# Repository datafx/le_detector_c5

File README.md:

# LE Gear Detector — XIAO ESP32-C5 Fork

Passive 5GHz/2.4GHz WiFi + BLE scanner for law-enforcement equipment,
rebuilt for the Seeed XIAO ESP32-C5 to add 5GHz detection. The original
project ([`datafx/le_detector`](https://github.com/datafx/le_detector),
ESP32-WROOM-32U) is 2.4GHz only and can't see the highest-value target
found in the field: Axon Fleet Hub units broadcasting their own hidden APs
on 5GHz. A match signals with a flashing red screen border + buzzer,
faster as the signal strengthens.

## Hardware

| Part | Notes | Link |
|---|---|---|
| Seeed Studio XIAO ESP32-C5 | RISC-V, dual-band WiFi 6 (2.4+5GHz), BLE 5, USB-C | [Seeed Studio](https://www.seeedstudio.com/Seeed-Studio-XIAO-ESP32C5-p-6609.html) |
| 2.8" ILI9341 TFT, SPI, 240×320, with XPT2046 touch + microSD slot | Standard combo board sold under many names; touch and SD are present on the board but not yet used by this firmware | search "2.8 inch ILI9341 SPI touch SD" |
| Active buzzer module, 3-pin (VCC/GND/signal) | Must have its own driver transistor onboard. Confirmed **active-low** on this build — check `BUZZER_ACTIVE_LOW` in `config.h` against yours | search "active buzzer module 3 pin" |
| Alfa APA-M25 dual-band antenna | 8 dBi @2.4GHz / 10 dBi @5GHz, RP-SMA | [Alfa Network](https://alfa-network.eu/apa-m25) |
| U.FL → RP-SMA pigtail | Connects the XIAO's onboard U.FL to the external antenna | search "U.FL RP-SMA pigtail" |
| Breadboard + jumper wires | | |
| USB-C cable | Power + programming | |

The display, buzzer, and pigtail are generic commodity parts sold by many
sellers under many names — there's no single canonical listing worth
linking (and one that works today can vanish tomorrow), so a search term
is given instead of a storefront link.

## Wiring

Pin assignments confirmed against the physical board — see `CLAUDE.md`
decision #6 for the full reasoning, including which pins were deliberately
avoided and why (boot-strap pins, reserved for a future GPS UART, etc.).

| Signal | XIAO pin | GPIO | Notes |
|---|---|---|---|
| Display `VCC` | `5V` | — | needs the 5V/VBUS pin specifically, not `3V3` |
| Display `GND` | `GND` | — | |
| Display `LED` (backlight) | `5V` | — | tied permanently on |
| Display `CS` | `D2` | 25 | |
| Display `DC` | `D3` | 7 | |
| Display `RESET` | `D4` | 23 | |
| Display `SDI`/MOSI | `D10` | 10 | shared SPI bus |
| Display `SCK` | `D8` | 8 | shared SPI bus |
| Display `SDO`/MISO | `D9` | 9 | shared SPI bus |
| `SD_CS` | `D5` | 24 | wired and reserved — SD support isn't built yet |
| `SD_MOSI`/`SD_MISO`/`SD_SCK` | `D10`/`D9`/`D8` | 10/9/8 | shared with the display |
| Buzzer `VCC` | `3V3` | — | |
| Buzzer `GND` | `GND` | — | |
| Buzzer signal | `D0` | 1 | |

Touch (`T_CLK`/`T_CS`/`T_DIN`/`T_DO`/`T_IRQ`) is present on the display
board but intentionally unwired — planned for future bench-configuration
tooling, not for driving controls.

## Build & flash

PlatformIO has no ESP32-C5 support as of this writing — this project
builds via the Arduino IDE / `arduino-cli` instead.

### Arduino IDE

1. **Install the ESP32 board package.** File → Preferences → Additional
   Boards Manager URLs, add:

       https://raw.githubusercontent.com/espressif/arduino-esp32/gh-pages/package_esp32_index.json

   Then Tools → Board → Boards Manager, search "esp32", install **esp32 by
   Espressif Systems**, version **3.3.5 or higher** (built and tested
   against 3.3.11).

2. **Select the board:** Tools → Board → esp32 → **XIAO_ESP32C5**.

3. **Install libraries** via Library Manager: `Adafruit GFX Library`,
   `Adafruit BusIO`, `Adafruit ILI9341`. BLE support is bundled with the
   esp32 core itself — no separate BLE library install needed.

4. **Open the sketch:** `firmware/le_detector_c5/le_detector_c5.ino`.
   Every `.cpp`/`.h` file in that same folder is compiled and linked
   automatically — Arduino sketches don't use PlatformIO's `src`/`include`
   split, so everything lives flat in one folder.

5. **Plug in the board** via USB-C, select its port, and upload.

### arduino-cli

    arduino-cli core update-index
    arduino-cli config set board_manager.additional_urls https://raw.githubusercontent.com/espressif/arduino-esp32/gh-pages/package_esp32_index.json
    arduino-cli core install esp32:esp32@3.3.11
    arduino-cli lib install "Adafruit GFX Library" "Adafruit ILI9341"
    arduino-cli compile --fqbn esp32:esp32:XIAO_ESP32C5 firmware/le_detector_c5
    arduino-cli upload -p /dev/ttyACM0 --fqbn esp32:esp32:XIAO_ESP32C5 firmware/le_detector_c5

### If upload fails, or the board doesn't show up as a serial port

The C5 uses its SoC's own native USB-Serial/JTAG peripheral, not a separate
USB-serial chip — no CH340/CP210x driver needed — but that comes with its
own gotchas, all hit and resolved during this project's own bring-up:

- **Linux: the `cdc_acm` kernel module.** If `/dev/ttyACM0` never appears,
  check `lsmod | grep cdc_acm`; if missing, `sudo modprobe cdc_acm` (if
  *that* fails with "module not found," your running kernel doesn't match
  what's installed on disk — reboot). Your user also needs permission on
  the port: group `dialout` on Debian/Ubuntu, `uucp` on Arch-based distros.
- **Upload fails with "Invalid head of packet" or "Serial data stream
  stopped: possible serial noise or corruption."** Looks like a code or
  board problem, usually isn't — a USB hub between the board and the
  computer was the actual cause here. Plug directly into a root/motherboard
  port before suspecting anything else.
- **No serial monitor output.** `arduino-cli monitor` produced nothing in
  testing even with the board clearly running. On Linux, plain
  `cat /dev/ttyACM0` worked reliably instead, and conveniently triggers a
  fresh reset on open. This firmware doesn't print anything during normal
  operation anyway (the display is the real status output), so this mostly
  matters if you're debugging.

## Watchlist

**62 OUI entries** across law-enforcement radio, body/dash cam, vehicle
router/MDT, radar/lidar, ALPR, and lightbar equipment, plus **6 SSID
patterns** (5 real + one test/demo row). The full list, provenance, and
vendor-collision reasoning live as comments in the source files themselves
— those are what actually runs, so they're the version that can't drift out
of sync with reality:

- [`oui_table.cpp`](firmware/le_detector_c5/oui_table.cpp) — MAC OUI
  watchlist
- [`ssid_table.cpp`](firmware/le_detector_c5/ssid_table.cpp) — SSID
  watchlist (beacons, probe requests, probe responses)

A few vendors are **disabled by default** after field testing showed they
false-positive more than they help — commented out, not deleted, so each
is one edit away from re-enabling if that read ever turns out wrong:
**CradlePoint**, **Peplink**, **Pepwave**, **Vantiva**, **PRO-VISION**.
Comment a row back in (or out) to change what's active for most entries;
CradlePoint specifically is gated by an `EXCLUDE_VENDOR_CRADLEPOINT` toggle
at the top of `oui_table.cpp`. Run `test/test_oui.cpp` after any edit.

Want to test a local addition before submitting it upstream? Drop it in
`user_oui_table.cpp` instead — unsorted, just appended to.

### SSID watchlist

| Pattern | Label | Category |
|---|---|---|
| `PSP-MVR`    | PSP in-car video          | Body/car cam |
| `SP-MVR`     | PSP paired virtual AP     | Other |
| `PSP-TEST`   | PSP facility              | Other |
| `PSPWLAN`    | PSP facility              | Other |
| `PSP_UC`     | PSP facility voice        | Other |
| `LEDET-TEST` | TEST/DEMO — not real gear | Other |

All PSP rows are prefix matches, deliberately — a substring `CONTAINS
"PSP"` rule tested against real survey data matched several unrelated
civilian networks near the same facilities (a pet store, a retailer, a
private residence). The full prefix string, not the shared `PSP` fragment,
is what makes these safe to alert on. Same logic for `SP-MVR` vs.
`PSP-MVR`: kept as two explicit rows rather than one `CONTAINS "SP-MVR"`
rule, which would also match `PSP-MVR` (it contains "SP-MVR" as a
substring).

**Provenance:** confirmed via WiGLE survey data cross-checked against
three independent Pennsylvania State Police barracks in three different
troops, roughly 280km apart, all on matching Cisco hardware.
`PSP-MVR`/`SP-MVR` (Mobile Video Recorder, PSP's in-car video system) and
`PSP-TEST` were confirmed at all three sites; cross-site BSSID correlation
— matching Cisco OUI sub-ranges across independently surveyed locations,
not just a shared naming convention — confirms a single statewide
deployment, not coincidence. `PSPWLAN`/`PSP_UC` were observed at one site
only, so carry lower confidence until cross-checked elsewhere. Exact survey
locations and dates are kept in local, non-public notes rather than this
file.

**Known limitation:** these are fixed APs at barracks buildings, not
vehicle-mounted equipment. A hit on the road means a cruiser's in-car
client is directedly probing for one of these SSIDs while out of range of
the real AP — whether PSP in-car systems actually do that is untested in
the field. Treat a hit here as barracks-proximity, not confirmed mobile
detection, until that's verified.

## Confirmed agencies

| Agency | Status |
|---|---|
| Pennsylvania State Police (PSP) | Confirmed in the field by the project author |

That's the only agency confirmed so far, but detection isn't tied to PSP.
The strongest target, Axon Fleet in-car hubs, broadcast their own WiFi
access point on 5GHz from Axon's registered MAC prefix (`00:25:DF`), and the
detector matches that prefix rather than anything agency-specific. **Any
agency running in-car Axon WiFi APs should be picked up the same way.** The
same goes for the other OUI entries: they match the equipment maker, not
the department. The PSP SSID rows are the exception, since those names are
specific to PSP.

If you've confirmed a hit on another agency, see
[Contributing](#contributing) so it can be added here.

## How detection works

A three-band phase machine — only one of WiFi-5GHz / WiFi-2.4GHz / BLE can
be up at a time (one radio behind a dual-band diplexer, and it can't do
WiFi and BLE simultaneously either). Scheduling is 5GHz-dominant, based on
real drive data and a measured radio-switch cost on this specific board:

- **5GHz** sweeps continuously (9 non-DFS channels, ~2.7s/sweep) — the
  only long-range, continuous signal (beacons every ~100ms), and the
  primary detection path.
- **BLE** gets a short 400ms dip every 3rd 5GHz sweep, not every cycle —
  its realistic job is a close/stopped encounter lasting several seconds,
  not a sub-second highway pass, so it doesn't need constant attention.
- **2.4GHz** gets a brief 3-channel token check (1/6/11 only) every 8th
  sweep — contributes almost nothing on the road per the drive data (a
  barracks-proximity signal, not a mobile one), kept only as an occasional
  check.

Measured WiFi↔BLE switch cost on this board: **103ms** to switch into BLE,
**9ms** back out, with zero measured variance across repeated runs. See
[`firmware/05_radio_switch_timing/`](firmware/05_radio_switch_timing/) to
re-measure on different hardware. The "every N sweeps" cadence constants
(`BLE_EVERY_N_SWEEPS`, `WIFI_2G_EVERY_N_SWEEPS` in `config.h`) are starting
points to tune empirically, not a measured optimum.

A match's alert shows which band/radio caught it — e.g. "via 5GHz WiFi
OUI" or "SSID beacon (2.4GHz): PSP-MVR" — useful for telling a long-range
hit apart from a close BLE encounter at a glance.

## Known limits

- **One radio, three bands, time-sliced.** Only one of 5GHz WiFi / 2.4GHz
  WiFi / BLE is ever listening — during any other phase, that band is
  invisible. See "How detection works" above for the current schedule.
- **MAC randomisation.** Only public BLE addresses and non-randomised WiFi
  MACs carry a real OUI — randomised addresses are skipped, since their
  vendor bits are meaningless. SSID matching runs independently of this
  and is unaffected.
- **PSP SSID rows are barracks-proximity, not confirmed mobile detection.**
  See SSID watchlist provenance above.
- **SSID matching depends on what's actually broadcast.** A wildcard probe
  or hidden-SSID beacon carries no SSID bytes at all — nothing to match
  either way. Directed probe requests are a declining signal on modern
  phones (randomised MAC + wildcard probes only, roughly iOS/Android 2014-
  2017 onward), so this increasingly only catches older/embedded clients.
  Beacon/probe-response matching is unaffected by that trend.
- **No SD card support yet.** The display board has a microSD slot and the
  select pin (`SD_CS`) is wired, but CSV-based config/logging isn't built —
  the firmware runs entirely on its compiled-in tables for now.

## Tuning

Everything lives in `firmware/le_detector_c5/config.h`: band/channel
lists, sweep cadence, flash-rate endpoints (`RSSI_WEAK`/`RSSI_STRONG`,
`FLASH_PERIOD_SLOW`/`FAST`), alert hold time, and `BUZZER_ENABLED` for
silent bench testing.

## Contributing

The watchlist is only as good as the field data behind it, and the most
useful thing you can contribute is **[Kismet](https://www.kismetwireless.net/)
captures recorded near police vehicles**. If you can make some, get in
touch and I'll analyze them for OUIs and SSIDs worth adding.

- **More than one sample, from different areas, is much more useful than
  one.** A single capture can't separate a department's gear from whatever
  else happened to be nearby. Several captures from different places,
  vehicles or agencies show what they have in common, which is what makes
  a reliable watchlist entry.
- **Capture both bands.** Use an adapter that covers 5GHz as well as
  2.4GHz; the in-car gear that matters most is on 5GHz. Bluetooth is a
  bonus if your setup supports it.
- **Note the context** for each capture: date and time, rough location,
  the agency, and what was nearby (parked cruiser, passing traffic,
  barracks lot).
- **Don't post captures publicly.** They contain the MAC addresses and
  network names of everyone nearby, not just the police gear. Open a
  [GitHub issue](https://github.com/datafx/le_detector_c5/issues)
  to make contact, and we'll arrange a private way to send the files.
- **Listen only, from where you're allowed to be.** Kismet's default
  passive capture is all that's needed. Don't follow vehicles or get in
  the way of anyone working.

Watchlist changes land here first, with the unit test in
`test/test_oui.cpp`, and are then copied to the
[Waveshare port](https://github.com/datafx/le_detector_waveshare_c5). Bug
reports and fixes are welcome as issues or pull requests.

## License

GPLv3 (see `LICENSE`), matching the companion `rf_stalker` and
`police_oui_watchlist` projects, and the upstream `le_detector` project
this is forked from.

[`firmware/le_detector_c5/detector.cpp`](firmware/le_detector_c5/detector.cpp)
carries its own `SPDX-License-Identifier: MIT` line for the portions
adapted from nyanBOX — see the header comment in that file for exactly
what was adapted and what changed. Everything else in this repo is GPLv3.

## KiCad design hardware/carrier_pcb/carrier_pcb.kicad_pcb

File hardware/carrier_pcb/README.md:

# Carrier PCB — WORK IN PROGRESS, NOT FINISHED

Do not fabricate this board as-is. A physical prototype of the previous
revision was built and bench-tested - display, buzzer, and routing all
confirmed working - but that hands-on assembly surfaced real mechanical
issues (board length *and* J2 spacing, J3 position; see below), now
fixed and fully re-routed (0 unconnected items). This corrected revision
hasn't been physically built yet - see "What's NOT done."

## Mounting: held by the header, not screwed to the case

This board has **no mounting holes**. Earlier drafts gave it the same 4
holes as the display module, so it could bolt to the case's existing
corner bosses — but that only works by stacking both boards on the same
4 screws, which needs standoffs/spacers between them and a case
modification to deepen the bosses. Given how light this assembly is
(PCB + XIAO + buzzer), that's not worth it: the board is instead held
purely by its header engagement with the display board above it (which
keeps screwing to the case exactly as it did before this board existed).
If real-world vibration ever proves that insufficient, a dab of hot glue
between the two boards is the cheap fix — not designed in up front.

**History: chamfer → notch → narrowed board, each one fitting the real
case better than the last.** The first version used a 6mm diagonal
chamfer at each corner, sized off the display's datasheet hole margins
with no real measurement of the boss itself. A 1:1 scale printout
test-fit against the real case showed it wasn't close - the boss is a
rounded square, not the slim post the chamfer assumed. Measured it
properly off the case STL (top-down render, self-calibrated against the
model's own exact bounding box, not an assumed scale): roughly **7-8mm
across**. Switched to a square notch sized as large as the layout
allowed (7.3mm, capped by J1's own pad clearance) - still about 1mm
short of what the boss needed, an acknowledged unresolved gap at the
time.

**Resolved differently: don't dodge the bosses, don't reach them at
all.** User measured the case's actual clear channel between the two
bosses directly: **36.3mm wide** (the board's full 86mm length is fine,
the case was never tight there). The board became a **plain rectangle,
36.3mm × 86mm**, centered on J1 (which is the single widest feature at
33.02mm) rather than matching the display's full 50mm width. This
sidesteps the boss problem entirely instead of cutting around it - no
corner notches needed, and it also incidentally resolved a DRC
clearance warning on a user-routed TFT_SCK trace that had been sitting
close to the old, bigger notch. J1 keeps 1.04mm of copper-to-edge
clearance on each side (comfortably above the 0.5mm minimum), and J2/U1/
J3 were already well inside this narrower footprint with no changes
needed.

**Trimmed again: top edge pulled in to put J2 right on the edge too,
mirroring J1.** J1 sits 2.0mm (pin-center-to-edge) from the bottom edge.
J2 was still 4.96mm from the top edge, leaving unused board above it.
Pulled the top edge in to the same 2.0mm margin: new top edge at
**y=2.96** (was y=0), so the board is now **36.3mm × 83.04mm**. J2 gets
the same 1.40mm copper-to-edge clearance J1 already had. Both edits
(width and this height trim) were applied by editing the outline
directly in the routed file rather than regenerating from the script,
each time confirming no existing trace/via fell outside the new
boundary before committing to it - preserved all 64 of the user's
hand-routed segments through both changes, verified via DRC (0 errors)
each time.

**Now physically confirmed - and that confirmation found two more real
issues.** A physical prototype of the board (narrowed width, trimmed
top edge) was built and bench-tested: display, buzzer, and routing all
worked. But mounting the real display on the real board surfaced a
mechanical problem the digital fit couldn't catch: **the board was too
short, and the display sat tilted rather than straight.**

**First attempt at the fix was wrong - extending the board outline
alone doesn't change anything mechanically.** Initial diagnosis:
insufficient board material above J2 to physically back/support the
display once both headers were engaged. Extended the top edge back out
by 2mm (y=2.96 -> y=0.96) without moving J2 itself. User caught this
immediately: J2's position relative to J1 - the actual thing that
determines whether two header rows line up with the real display's true
spacing - never changed, so nothing about the mechanical fit could have
changed either; the board was just bigger, the tilt was still there.
**Real fix: move J2 the same 2mm, same direction, right along with the
edge** (y=4.96 -> 2.96) - not just extend the board around it. This
restores J2's margin-from-edge to exactly 2.0mm (matching J1's margin
again, same relationship as the original "J2 sits on the edge like J1"
decision) and - the part that actually matters mechanically -
**increases the J1-to-J2 spacing by 2mm** (79.04mm -> 81.04mm), which is
what a header-spacing mismatch against the real display would need.
Board is now **36.3 x 85.04mm**. J2 carries no electrical connections
(see below), so this move touched zero routing - verified via DRC (0
errors, segment/via count unchanged before and after).

**Also moved J3 (buzzer) closer to J1** (y=68 -> y=78, x unchanged) -
the real XIAO's USB-C connector was crowding the buzzer's right-angle
header in practice, something the digital layout didn't surface either
since courtyard-only clearance checks don't capture a mated cable's
real footprint. Moving J3 toward J1 trades its distance from U1's USB-C
area for more working room. Verified clear of J1's own pads (4.8mm
copper clearance) via DRC.

**Routing cost of this move: not trivial.** GND, BUZZER_SIG, and 3V3
are the only nets that touch J3, so only those needed clearing (12
segments + 2 vias, out of 41 total) - the other 26 segments (all the
TFT_* signal routing, untouched) survived intact. But GND turned out to
use J3's own pad as the junction point connecting J1 and U1's GND
together, not just a branch to J3 - so re-routing GND means redoing the
full 3-way connection, not just adding one short new segment. Checked
for other-net collisions at J3's new position before moving it (a TFT_CS
trace runs close by at x=15.71, confirmed 0.93mm clear) - also caught
and fixed a new silkscreen-over-copper warning from J3's own label
landing too close to J1's row in the tighter gap; moved the label to
the now much-larger open space on J3's other side instead.

**Still needs**: re-routing GND/BUZZER_SIG/3V3 (flagged above), and a
fresh physical test-fit of this corrected board - the tilt and USB-C
crowding were real-hardware findings, but this specific fix hasn't been
built yet.

## U1 (XIAO socket): footprint was wrong, now matches the real device

The original U1 footprint was a generic guess — two rows of 7 pins,
7.62mm apart, pins at `i*2.54mm` within each row — never checked against
the real XIAO ESP32-C5's actual pinout, and not mirrored for back-side
mounting. User caught both problems: wrong footprint, and backwards for
how the device actually gets plugged in (XIAO mounts on the board's
back, opposite the display).

**Fixed using Seeed's own official files**, not another guess:
downloaded their published KiCad footprint
(`XIAO-ESP32-C5-DIP.kicad_mod`) and schematic symbol from the
[XIAO KiCad library](https://wiki.seeedstudio.com/XIAO_BLE/) (same
family covers every XIAO board). The real footprint has **15.24mm**
between the two pin rows, not 7.62mm — a completely different part of
the board was being used. Cross-referenced the symbol to get the
real pin-number-to-signal mapping (D0–D6 on one row, D7–D10 + 3V3_OUT/
GND/VBUS on the other, in that specific order — not a clean split).

**Mirroring**: a part mounted on the back layer needs its footprint
mirrored left-right relative to how it would sit on the front — this is
what KiCad does automatically when you flip a footprint in the GUI, but
since this one was hand-authored as raw coordinates, that mirroring had
to be applied by hand too, and wasn't. Verified the mirror direction
using Seeed's own front and back pinout diagrams for the XIAO (they
publish both specifically because this flip is easy to get backwards) -
confirmed the two diagrams are exact left-right mirrors of each other
before trusting the derivation.

**Routing cleared, not preserved, for this one.** Unlike the earlier
outline-only changes (width, height trims), this moves the pads
themselves, and nearly every net touches U1 directly or routes through
it - preserving any of the old routing wasn't realistic. Pulled all 64
track/via segments rather than leave something uncertain in place.
Board is back to a clean, DRC-verified ratsnest (0 errors, 12
unconnected items, matching the exact pre-routing baseline) - **needs a
full re-route**.

**Slid toward the board's right edge** for USB-C cable clearance, as
far as the *real device's physical body* allows - not just its pads.
The pads alone would have permitted sliding further right, but the
actual XIAO module extends ~2.8mm beyond its own pin span on each side;
checking pads only would have let the real part hang ~1.3mm off the
board edge. Capped at **x=32** (board right edge minus the real
courtyard extent minus a 0.5mm margin), not x=34.

**Flagging, not deciding, one open question**: with this as a straight
slide (no rotation), the XIAO's USB-C port faces *inward* (toward
x≈21-23, the board's open left-center area), not toward the right edge
itself - it's the *blank far end* of the device that now sits near the
right edge. This still frees up real approach space for a cable (the
whole left side of U1's row is now open board), but if the port itself
needs to be at/past the edge, that needs a 180° rotation on top of the
slide, which hasn't been done - flagging it rather than guessing, since
it changes which end of the board needs clearance.

## J3 (buzzer socket): pin order changed, moved left, now a right-angle header

**Pin order**: was VCC/GND/SIG (pins 1/2/3). Changed to **GND/SIG/VCC**
(pins 1/2/3) to match the physical pinout of the actual buzzer module
being used. Schematic symbol's pin names updated to match (so the
symbol doesn't show "pin 1 = VCC" while actually wired to GND) - J3's
physical pad *positions* didn't change for this part, only which net
each pad carries.

**Position**: moved from x=20 to **x=9** (pins span 9.00-14.08), clear
of both the board's left edge (1.55mm pad clearance) and U1's real
device body (6.77mm clear of U1's courtyard at x≈21.45) - U1 having
moved right made room for this.

**Right-angle (90°) header, not straight** - so the buzzer module can
lie flat against the back of the carrier instead of standing up
perpendicular on pins. This is a BOM/part-choice change, not a PCB
layout change: a right-angle header's hole pattern is the same 3 pads
at the same pitch, just a different physical part populated there -
reflected in `BOM.md`, `bom.csv`, and the schematic's own description
field for J3.

**Standoff height: not chosen - a real open question, not a guess I'm
comfortable making.** The buzzer board needs to lie flat without
touching a USB-C cable plugged into U1's port. Getting that number
right needs several real measurements I don't have verified: U1's own
header standoff height (never specified - it's just "a 2x7 female
header" with no particular part/height chosen either), the XIAO's USB-C
receptacle height above its own PCB (datasheet has no Z-axis dimension,
only the 21x17.8mm footprint), and critically, **the actual cable's
plug profile** - which isn't a XIAO spec at all, it varies by which
cable gets used, from slim low-profile plugs to bulky ones. A header
spec sheet can't tell me that part. **Recommend a physical mockup**
once the real parts are in hand (XIAO + a header + the actual cable
likely to be used) rather than trusting a number derived from
incomplete datasheets - or tell me the exact cable/header part numbers
if there's a specific one in mind and I can look up real dimensions for
those two at least.

## J2 (SD header socket): populated, not wired

J2 is on the board purely so the display module has somewhere to plug
its SD header into for mechanical support — pulling one corner of the
display without it would leave that corner unsupported by anything but
J1. It carries **no electrical connections**: all 4 pins (and U1's
SD_CS pin, which would otherwise drive it) are explicit no-connects.
SD card bring-up (mount, read, CSV config/logging) is a real future
goal, not abandoned, but it's down the road enough that wiring it now
would just be unused complexity - revisit as part of a later PCB
revision, likely alongside touch support.

**The display doesn't come with a header there to plug in** - the
MSP2807's SD pads ship unpopulated (confirmed from the datasheet). A
1×4 male header needs to be hand-soldered onto the display board itself
before it has anything to mate with J2 - added to `BOM.md`.

**Position re-measured and corrected.** The first placement (18.40,
11.00) was a rough visual estimate. Re-measuring the datasheet image
found the estimate was based on an incorrect pixel-to-mm scale (assumed
a literal 1:1 300dpi-to-mm render; the PDF's actual scale, derived from
the two known hole-spacing dimensions, is ~9.05px/mm, not ~11.81).
Corrected position: **(21.15, 4.96)** — the 4 SD pads sit at essentially
the same height as the top mounting holes, not ~11mm down as first
estimated. Pitch was already right (standard 2.54mm). Still a datasheet
*image* measurement, not a direct physical check — reasonably confident
now, but confirm against the real board before fabricating.

## Silkscreen: functional labels, pin-1 markers, and a real bug fixed

Added on request - before this, silkscreen was just 4 bare reference
designators (J1/J2/J3/U1), nothing else, no graphics at all.

- **Functional labels** on all 4 connectors, stating what they are *and*
  which side of the board the part goes on: `DISPLAY — FRONT` (J1),
  `SD (NC) — FRONT` (J2), `XIAO — BACK` (U1), `BUZZER — BACK` (J3).
- **Pin-1 markers**: pin 1 of every connector is now a square pad
  instead of round (standard convention) - J2 and J3 didn't strictly
  need it since they're asymmetric/small, but did it for all 4 for
  consistency and because this board has already had two real
  orientation bugs this session (U1's mirroring, J3's pin order) - cheap
  insurance against a third one during assembly.
- **Board title**: `LE Detector C5 by datafx Rev 2` (" Rev 2" appended
  once this revision's fixes - board length, J2 spacing, J3 position -
  landed, so a built board is traceable to which design it matches).
  2.2mm text (noticeably
  larger than the 1mm connector labels), vertical along the left edge,
  top-justified. Placed on the back (B.SilkS) rather than the front -
  the display covers nearly the full front face once plugged into J1
  (its own board is as tall as this carrier, header near its bottom
  edge), so front silkscreen would be hidden after assembly; the back
  stays mostly open even with U1/J3 populated. Positioned clear of both
  U1 and J3, confirmed via DRC and a true flipped-back render (not just
  the see-through view) before trusting it, per the mirroring lesson
  just below.

**Found and fixed a real bug while verifying this, not a new one
introduced by it: back-layer silkscreen text was never actually
mirrored.** DRC has been flagging `nonmirrored_text_on_back_layer` on
U1's and J3's reference labels since they were first created, and it
was dismissed every single time as the same cosmetic baseline as the
`lib_footprint_issues` warnings - it isn't. Rendered the board with
`kicad-cli`'s `-m` flag (true "physically flip the board and look at
the back" view, not the usual "see-through from the front" renders used
throughout this project) and the text came out genuinely backwards -
`U1`, `J3`, and both new back-side labels all read right-to-left,
garbled. This would have printed wrong on the real board. Fixed by
adding `(justify mirror)` to all 4 back-layer text elements (the 2
existing reference labels plus the 2 new functional labels) - verified
again with the same true-flip render, now reads correctly. **Re-check
any future back-layer text added to this board the same way** (render
with `-m`, don't trust the normal see-through view) - this bug is easy
to reintroduce since hand-authored S-expressions don't get KiCad's
automatic GUI-flip mirroring for free.

## What's done and verified

- **Schematic** (`carrier_pcb.kicad_sch`) — complete, ERC-clean (0 errors).
  Every net matches the locked pin table in the project's own notes.
- **PCB footprint placement** (`carrier_pcb.kicad_pcb`) — board outline
  (36.3×85.04mm rectangle, see above) and the display's main header
  position taken directly from the MSP2807 display's own datasheet, not
  estimated. DRC-verified: every pad is on the correct net
  (ratsnest-correct), 0 real errors.
- **U1 footprint** now matches Seeed's official XIAO-ESP32-C5-DIP
  footprint, correctly mirrored for back-side mounting (see above).
  **Confirmed on real hardware** - a physical prototype was built and
  bench-tested, display and buzzer both working.
- **Silkscreen** — functional labels + pin-1 markers on all 4
  connectors, back-layer text verified correctly mirrored (see above).
- **Solder side for all 4 connectors** — verified directly from each
  footprint's stored layer field (not just visually): J1/J2 on `F.Cu`
  (front), U1/J3 on `B.Cu` (back), matching their silkscreen labels.
- **Routing** — GND/BUZZER_SIG/3V3 re-routed by the user after J3's move
  (see above). DRC clean: 0 errors, **0 unconnected items** - all 10
  nets fully routed.

## What's NOT done

- **SD header position** (J2) is re-measured and corrected (see above)
  but still a datasheet-image measurement, not a direct physical check —
  verify against the physical display board before finalizing. Its Y
  position has now been corrected twice from that original estimate
  (datasheet re-measurement, then the 2mm spacing fix above) - a
  physical check is overdue before trusting it a third time.
- **No future USB-C panel connector or pigtail** designed yet — the case
  already has a wire-passthrough cutout reserved for this, but the
  connector and cable routing aren't part of this board yet.
- **No physical test-fit of *this* corrected board yet** — the tilt and
  USB-C crowding that prompted this revision were found on the
  *previous* physical prototype; this fix (board + J2 both 2mm, J3
  moved, fully re-routed) hasn't been built and tested itself yet. The
  outline is sized against the user's own case measurement (36.3mm
  clear channel) and J1-J2 spacing against a direct user correction, not
  yet confirmed hands-on with the actual board.

## Fits the case in `../../case/` (also WIP — see its README)

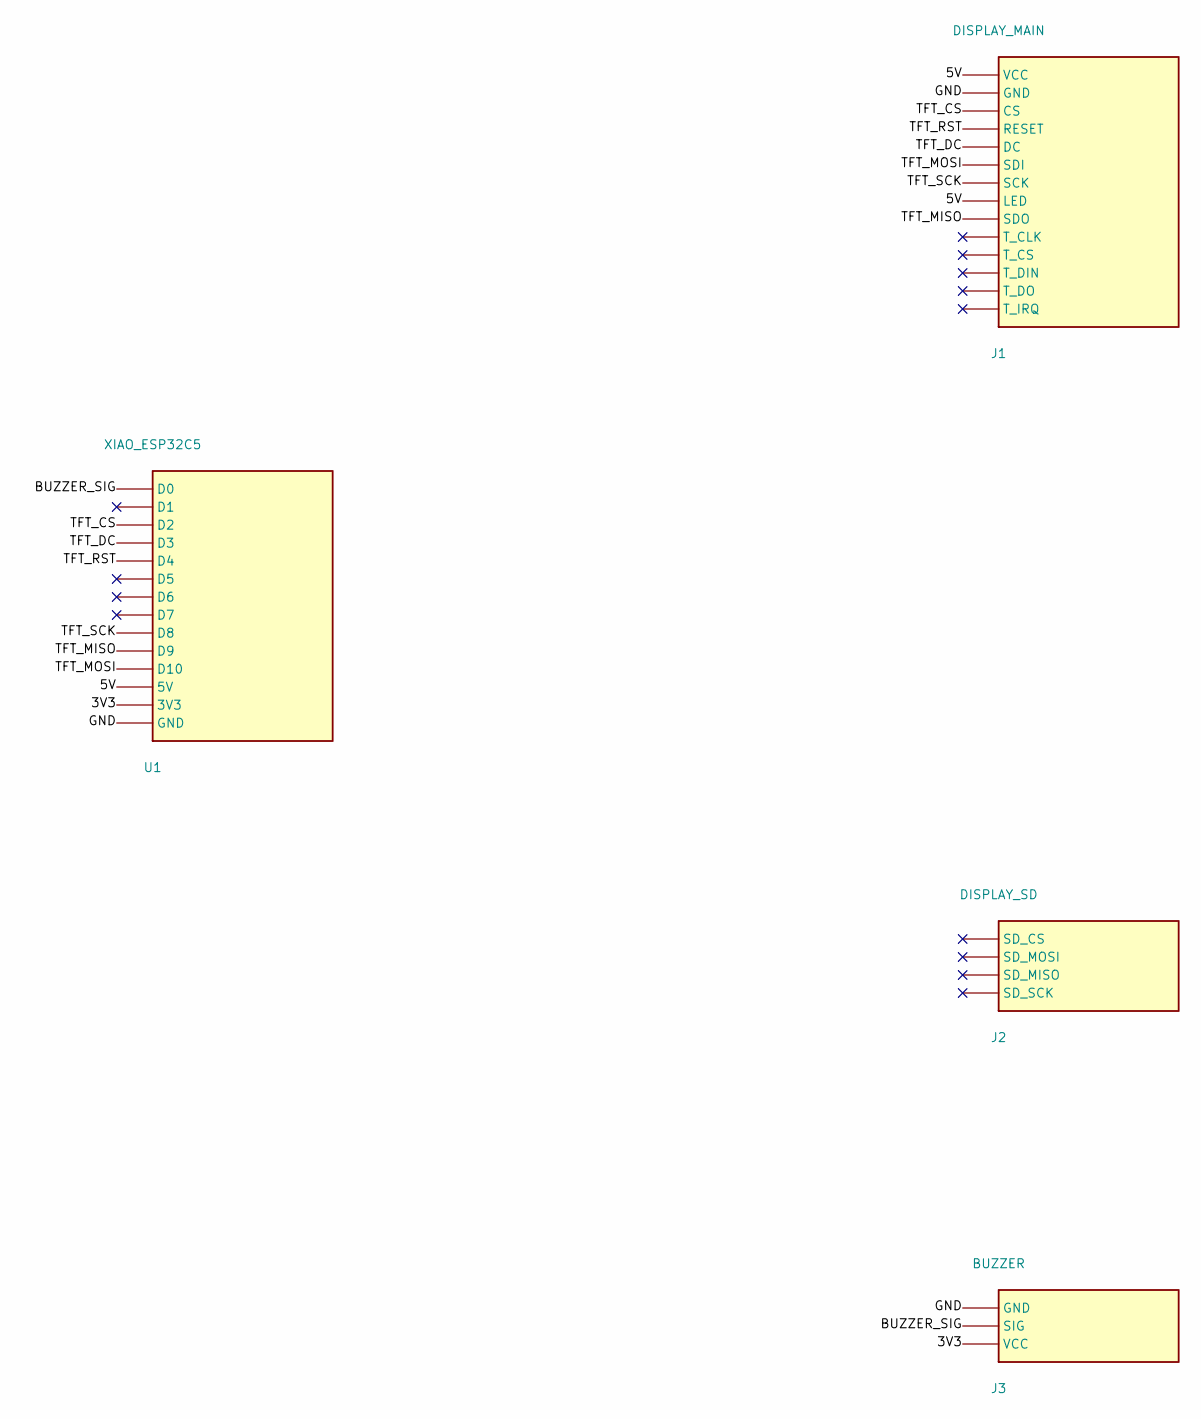
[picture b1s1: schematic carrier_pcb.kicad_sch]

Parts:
J1: DISPLAY_MAIN
J2: DISPLAY_SD
J3: BUZZER
U1: XIAO_ESP32C5

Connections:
3V3: J3.3 (VCC), U1.13 (3V3)
5V: J1.1 (VCC), J1.8 (LED), U1.12 (5V)
BUZZER_SIG: J3.2 (SIG), U1.1 (D0)
GND: J1.2 (GND), J3.1 (GND), U1.14 (GND)
TFT_CS: J1.3 (CS), U1.3 (D2)
TFT_DC: J1.5 (DC), U1.4 (D3)
TFT_MISO: J1.9 (SDO), U1.10 (D9)
TFT_MOSI: J1.6 (SDI), U1.11 (D10)
TFT_RST: J1.4 (RESET), U1.5 (D4)
TFT_SCK: J1.7 (SCK), U1.9 (D8)

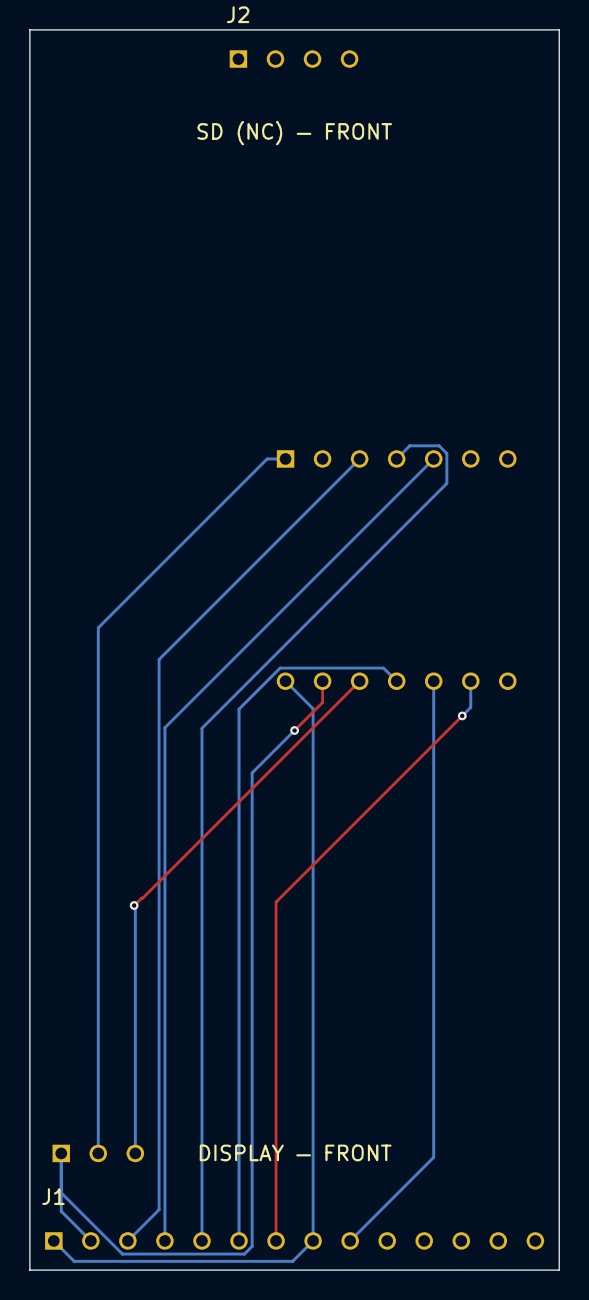
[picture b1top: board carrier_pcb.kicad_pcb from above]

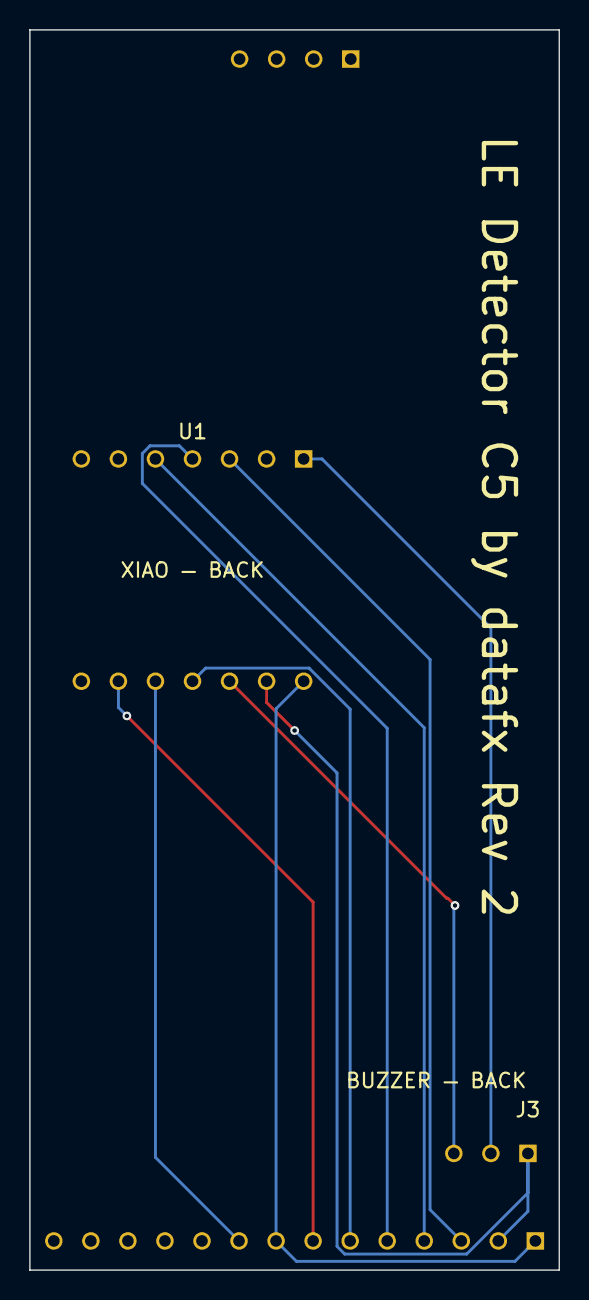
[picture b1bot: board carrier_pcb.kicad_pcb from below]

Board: 2 copper layers, 36.3 x 85.0 mm, 4 parts (2 on the bottom side), 10 nets.

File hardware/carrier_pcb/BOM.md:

# Carrier PCB — Bill of Materials

## Parts to populate on the carrier PCB

Generated from the schematic (`kicad-cli sch export bom`) — see `bom.csv`
for the raw export.

| Ref | Qty | Description |
|---|---|---|
| J1 | 1 | 1×14 female header, 2.54mm pitch — socket for MSP2807 display main header |
| J2 | 1 | 1×4 female header, 2.54mm pitch — socket for MSP2807 SD header (**mechanical only, not wired** — see README) |
| J3 | 1 | 1×3 **right-angle (90°)** female header, 2.54mm pitch — socket for 3-pin active buzzer module, lets the buzzer board lie flat against the carrier instead of standing up on pins. **Standoff height not yet chosen** — must clear a USB-C cable plugged into U1, see README. |
| U1 | 1 | 2×7 female header, 2.54mm pitch — socket for Seeed XIAO ESP32-C5 |

## Mounting hardware

None. This board isn't screwed to the case — it's held by the header
engagement with the display board above it, which keeps its own original
4 screws/standoffs into the case's corner bosses unchanged. A dab of hot
glue between the carrier PCB and the display board is the fallback if
testing ever shows the header connection alone isn't enough — not
included here since it's a maybe-needed-later item, not a planned part.

## Plug-in modules (not populated on the carrier PCB)

These mate with the sockets above rather than being soldered to the
carrier board. Already documented with sourcing links in the project
[README](../../README.md#hardware) — not duplicated here to avoid two
copies drifting out of sync:

- Seeed Studio XIAO ESP32-C5 → plugs into U1
- MSP2807 2.8" display module → plugs into J1 + J2 (see below — J2's
  side needs a header added to the display board itself first)
- 3-pin active buzzer module → plugs into J3

## Parts needed on the display module itself (not included with it)

| Part | Qty | Notes |
|---|---|---|
| 1×4 male header, straight, 2.54mm pitch | 1 | The MSP2807 ships with its SD-header pads **unpopulated** — confirmed from the datasheet, this isn't a stock part of the board. Hand-solder one onto those pads so the display has pins to plug into J2. Purely mechanical (J2 carries no signals — see README); any 1×4 straight male header works, doesn't need to match any particular spec beyond 2.54mm pitch to fit the pads. |

## Not yet in this BOM

- Future USB-C panel-mount connector + internal pigtail cable (per the
  wire-passthrough cutout already in the case) — not designed yet.

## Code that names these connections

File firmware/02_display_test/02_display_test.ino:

// Bring-up step 2: ILI9341 display "hello world" over SPI.
// Adafruit_ILI9341 + Adafruit_GFX per CLAUDE.md decision #5 (TFT_eSPI has
// no ESP32-C5 support yet). Pins per decision #6.

#include <SPI.h>
#include <Adafruit_GFX.h>
#include <Adafruit_ILI9341.h>

#define TFT_CS   25
#define TFT_DC    7
#define TFT_RST  23
#define TFT_SCK   8
#define TFT_MISO  9
#define TFT_MOSI 10

Adafruit_ILI9341 tft(TFT_CS, TFT_DC, TFT_RST);

void setup() {
  SPI.begin(TFT_SCK, TFT_MISO, TFT_MOSI, TFT_CS);
  tft.begin();
  tft.setRotation(1);
  tft.fillScreen(ILI9341_BLACK);

  tft.setTextColor(ILI9341_GREEN);
  tft.setTextSize(3);
  tft.setCursor(10, 10);
  tft.println("LE Detector C5");

  tft.setTextColor(ILI9341_WHITE);
  tft.setTextSize(2);
  tft.setCursor(10, 60);
  tft.println("Display OK");
}

void loop() {
}
